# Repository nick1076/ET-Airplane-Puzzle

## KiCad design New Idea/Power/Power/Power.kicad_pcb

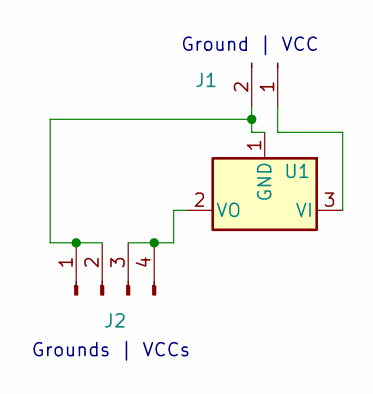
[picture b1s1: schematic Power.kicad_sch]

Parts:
J1: Conn_PinHeader_1x02_P2.54mm_Horizontal_SMD; PinHeader_UPDI_01x02_P2.54mm_Horizontal_SMD
J2: Conn_PinHeader_1x04_P2.54mm_Horizontal_SMD; PinHeader_1x04_P2.54mm_Horizontal_SMD
U1: Regulator_Linear_NCP1117-5.0V-1A; SOT-223-3_TabPin2

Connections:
unnamed: J1.1, U1.3 (VI)
unnamed: J1.2, J2.1, J2.2, U1.1 (GND)
unnamed: J2.3, J2.4, U1.2 (VO)

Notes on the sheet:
Grounds | VCCs
Ground | VCC

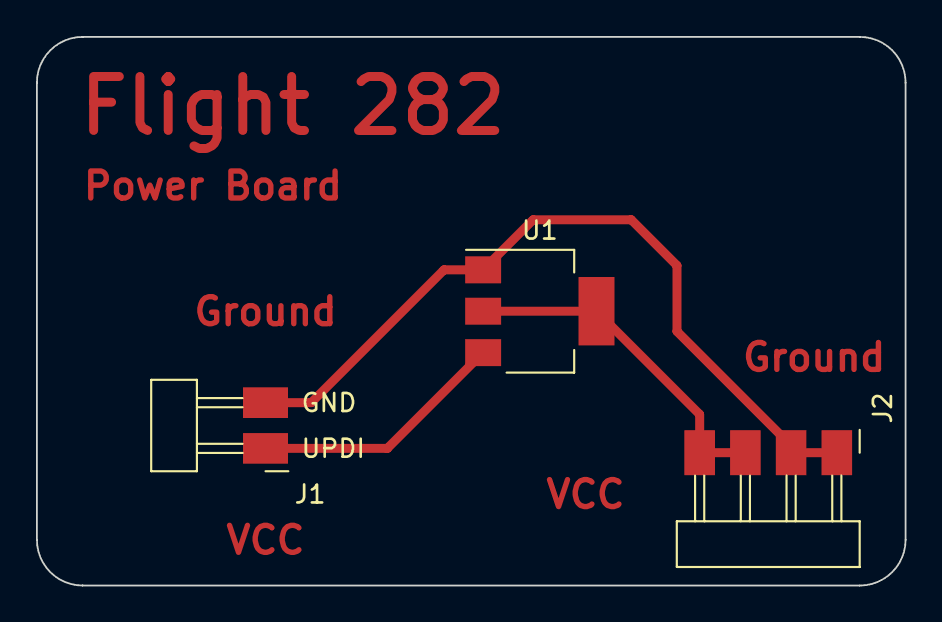
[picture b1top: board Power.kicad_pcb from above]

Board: 2 copper layers, 48.3 x 30.5 mm, 3 parts (0 on the bottom side), 3 nets.

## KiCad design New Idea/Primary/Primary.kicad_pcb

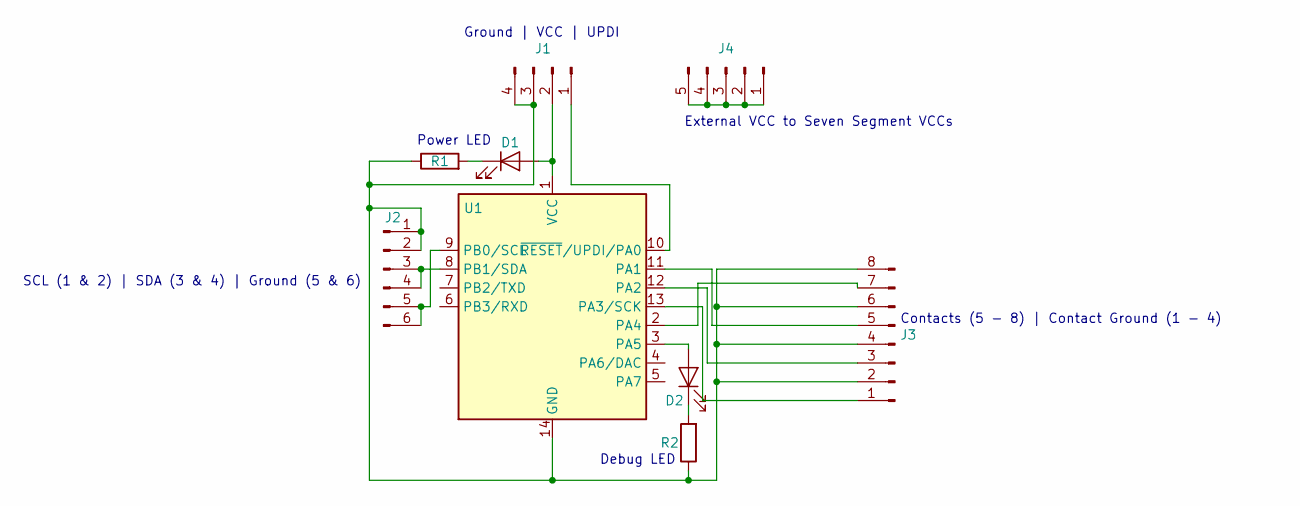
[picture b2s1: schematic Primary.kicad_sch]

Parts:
D1, D2: LED; LED_1206
J1: Conn_PinHeader_1x04_P2.54mm_Horizontal_SMD; PinHeader_1x04_P2.54mm_Horizontal_SMD
J2: Conn_PinHeader_1x06_P2.54mm_Horizontal_SMD; PinHeader_1x06_P2.54mm_Horizontal_SMD
J3: Conn_PinHeader_1x08_P2.54mm_Vertical_THT_D1.4mm; PinHeader_2x04_P2.54mm_Vertical_SMD
J4: Conn_PinHeader_1x05_P2.54mm_Horizontal_SMD; PinHeader_1x05_P2.54mm_Horizontal_SMD
R1, R2: R; R_1206
U1: Microcontroller_ATtiny1614-SSFR; SOIC-14_3.9x8.7mm_P1.27mm

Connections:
unnamed: D1.1 (K), R1.2
unnamed: D1.2 (A), J1.2, U1.1 (VCC)
unnamed: D2.1 (K), R2.2
unnamed: D2.2 (A), U1.3 (PA5)
unnamed: J1.3, J1.4, J2.1, J2.2, J3.2, J3.4, J3.6, J3.8, R1.1, R2.1, U1.14 (GND)
unnamed: J2.3, J2.4, U1.8 (PB1/SDA)
unnamed: J2.5, J2.6, U1.9 (PB0/SCL)
unnamed: J3.1, U1.13 (PA3/SCK)
unnamed: J3.3, U1.12 (PA2)
unnamed: J3.5, U1.11 (PA1)
unnamed: J3.7, U1.2 (PA4)
unnamed: J4.1, J4.2, J4.3, J4.4, J4.5
unnamed: J1.1, U1.10 (~RESET/UPDI/PA0)

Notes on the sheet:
Power LED
External VCC to Seven Segment VCCs
Debug LED
Ground | VCC | UPDI
SCL (1 & 2) | SDA (3 & 4) | Ground (5 & 6)
Contacts (5 - 8) | Contact Ground (1 - 4)

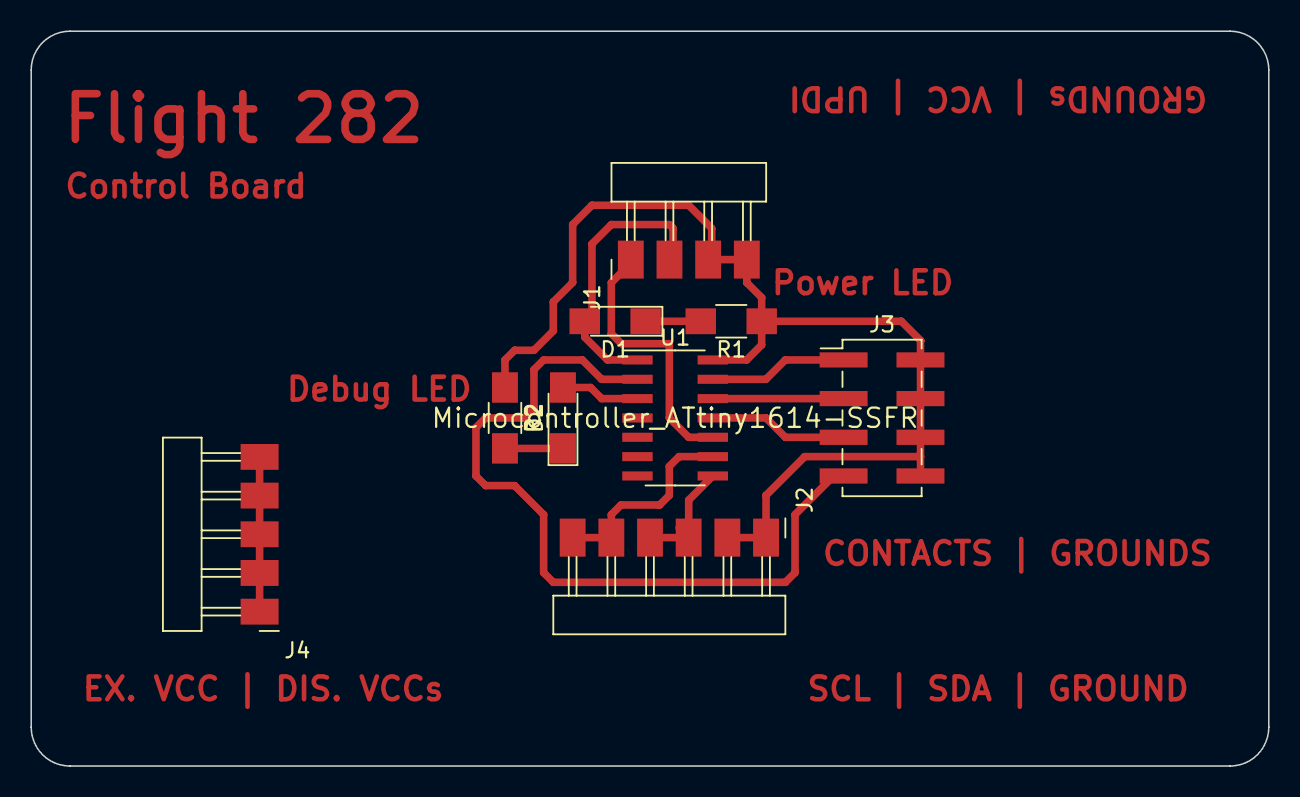
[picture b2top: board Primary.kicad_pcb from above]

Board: 2 copper layers, 81.3 x 48.3 mm, 9 parts (0 on the bottom side), 13 nets.

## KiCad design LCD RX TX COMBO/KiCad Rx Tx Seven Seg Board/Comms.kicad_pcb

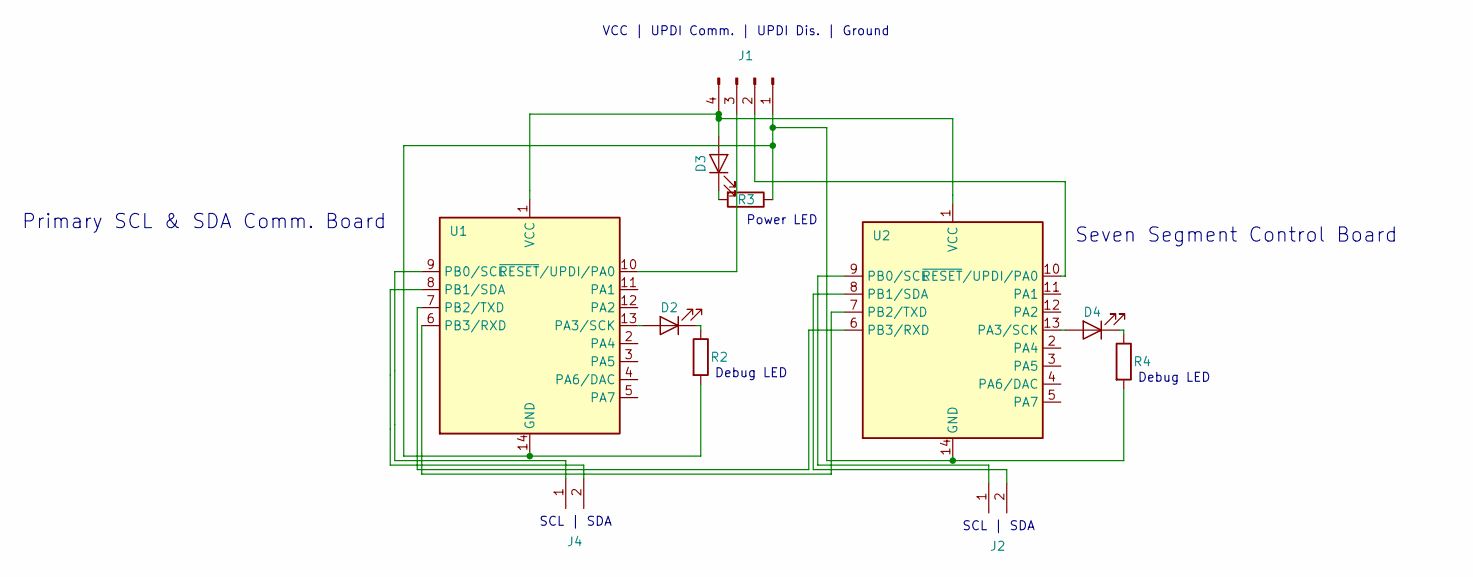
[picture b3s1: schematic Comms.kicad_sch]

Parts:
D2, D3, D4: LED; LED_1206
J1: Conn_PinHeader_1x04_P2.54mm_Horizontal_SMD; PinHeader_1x04_P2.54mm_Horizontal_SMD
J2, J4: Conn_PinHeader_1x02_P2.54mm_Horizontal_SMD; PinHeader_UPDI_01x02_P2.54mm_Horizontal_SMD
R2, R3, R4: R; R_1206
U1, U2: Microcontroller_ATtiny1614-SSFR; SOIC-14_3.9x8.7mm_P1.27mm

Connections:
unnamed: D2.1 (K), R2.1
unnamed: D2.2 (A), U1.13 (PA3/SCK)
unnamed: D3.1 (K), R3.2
unnamed: D3.2 (A), J1.4, U1.1 (VCC), U2.1 (VCC)
unnamed: D4.1 (K), R4.1
unnamed: D4.2 (A), U2.13 (PA3/SCK)
unnamed: J2.1, U2.9 (PB0/SCL)
unnamed: J2.2, U2.8 (PB1/SDA)
unnamed: J4.1, U1.9 (PB0/SCL)
unnamed: J1.1, R2.2, R3.1, R4.2, U1.14 (GND), U2.14 (GND)
unnamed: U1.6 (PB3/RXD), U2.7 (PB2/TXD)
unnamed: U1.7 (PB2/TXD), U2.6 (PB3/RXD)
unnamed: J4.2, U1.8 (PB1/SDA)
unnamed: J1.3, U1.10 (~RESET/UPDI/PA0)
unnamed: J1.2, U2.10 (~RESET/UPDI/PA0)

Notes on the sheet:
Primary SCL & SDA Comm. Board
Debug LED
Seven Segment Control Board
SCL | SDA
VCC | UPDI Comm. | UPDI Dis. | Ground
Power LED

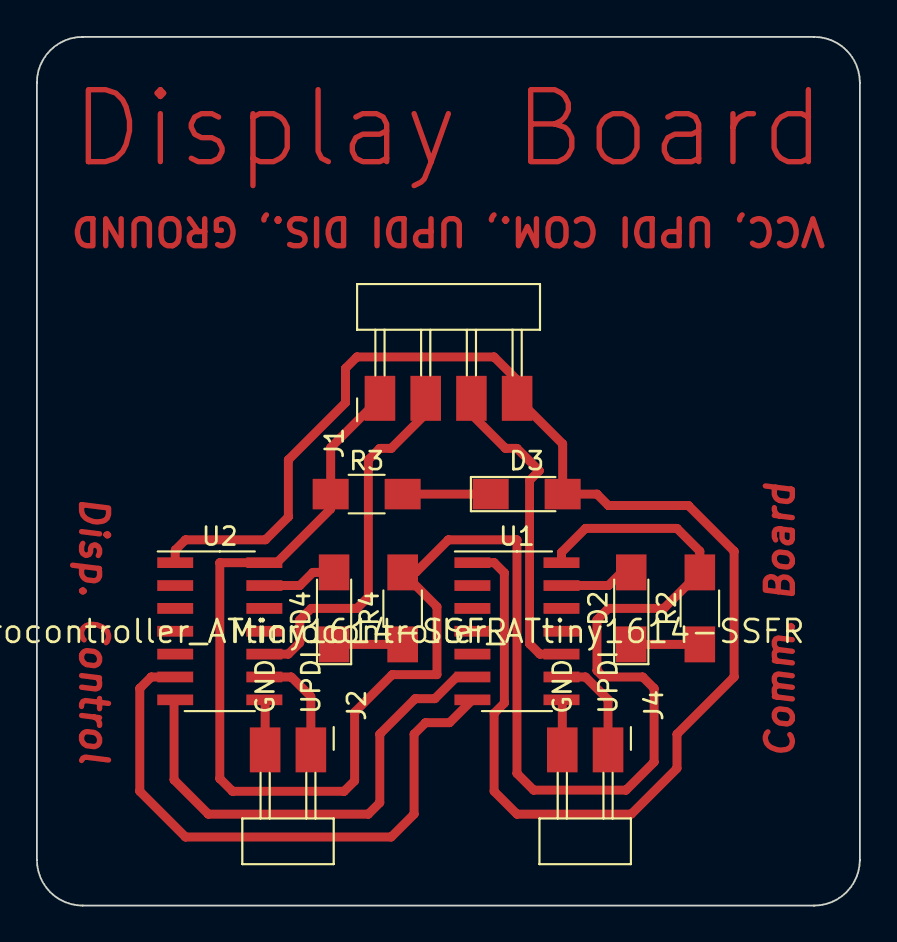
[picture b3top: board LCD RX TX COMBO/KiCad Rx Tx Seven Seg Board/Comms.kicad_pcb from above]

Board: 2 copper layers, 45.7 x 48.3 mm, 11 parts (0 on the bottom side), 15 nets.

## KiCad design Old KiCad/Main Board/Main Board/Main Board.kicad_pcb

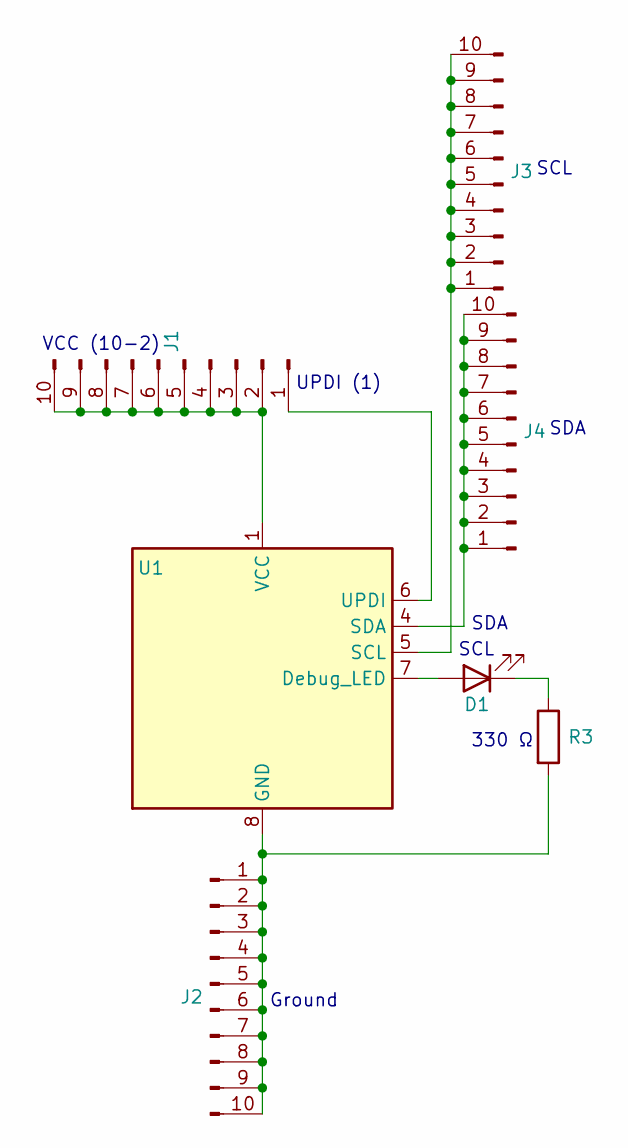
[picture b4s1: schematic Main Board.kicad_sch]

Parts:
D1: LED; LED_1206
J1, J2, J3, J4: Conn_01x10_Male; PinHeader_1x10_P2.54mm_Horizontal_SMD
R3: R; R_1206
U1: ATtiny412-SS; SOIC-8_3.9x4.9mm_P1.27mm

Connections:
unnamed: D1.1 (K), R3.1
unnamed: D1.2 (A), U1.7 (Debug_LED)
unnamed: J1.1, U1.6 (UPDI)
unnamed: J1.2, J1.3, J1.4, J1.5, J1.6, J1.7, J1.8, J1.9, J1.10, U1.1 (VCC)
unnamed: J2.1, J2.2, J2.3, J2.4, J2.5, J2.6, J2.7, J2.8, J2.9, J2.10, R3.2, U1.8 (GND)
unnamed: J3.1, J3.2, J3.3, J3.4, J3.5, J3.6, J3.7, J3.8, J3.9, J3.10, U1.5 (SCL)
unnamed: J4.1, J4.2, J4.3, J4.4, J4.5, J4.6, J4.7, J4.8, J4.9, J4.10, U1.4 (SDA)

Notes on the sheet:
SCL
VCC (10-2)
SDA
UPDI (1)
Ground
330 Ω

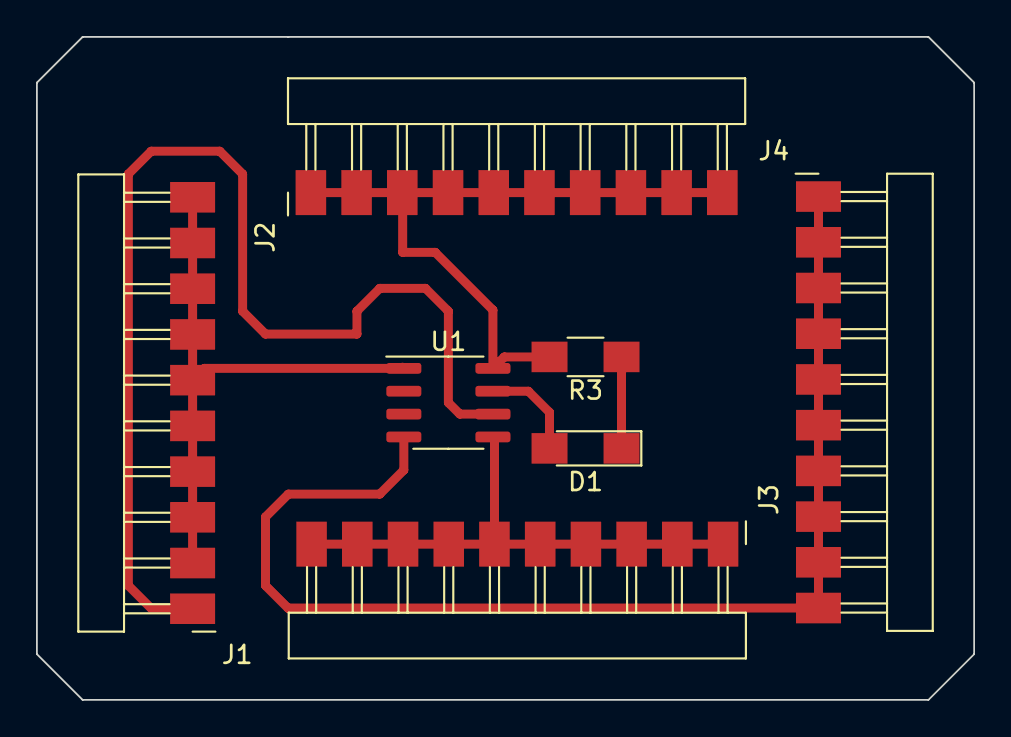
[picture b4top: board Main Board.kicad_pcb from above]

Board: 2 copper layers, 52.1 x 36.8 mm, 7 parts (0 on the bottom side), 7 nets.

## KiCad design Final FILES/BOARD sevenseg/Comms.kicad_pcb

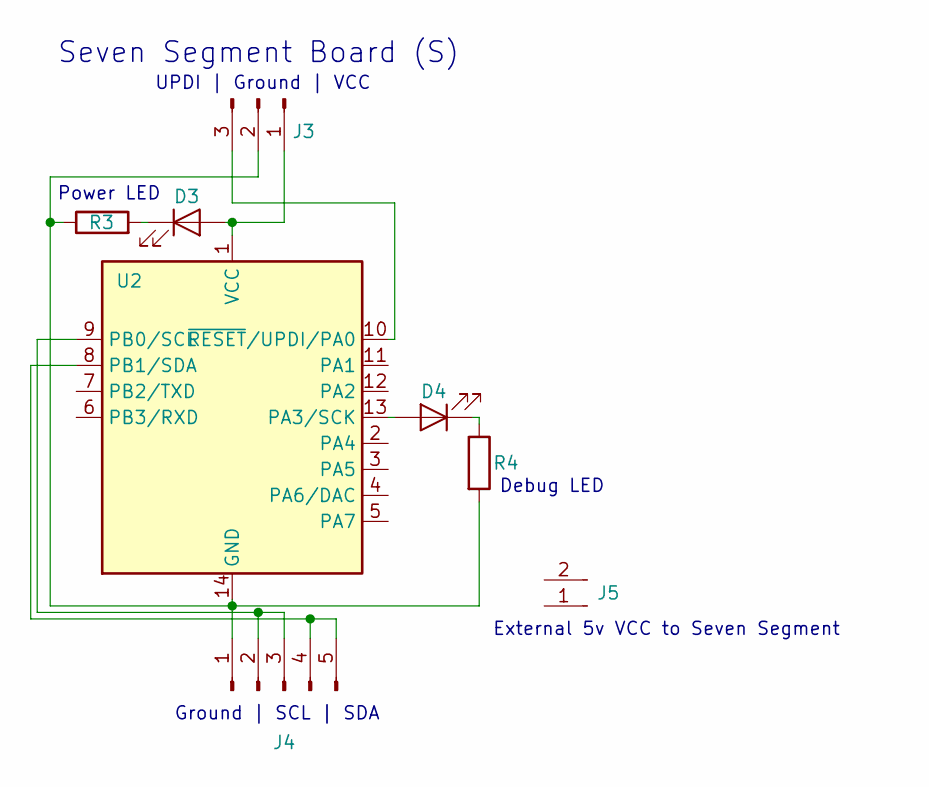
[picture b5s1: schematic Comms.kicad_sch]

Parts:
D3, D4: LED; LED_1206
J3: Conn_PinHeader_1x03_P2.54mm_Horizontal_SMD; PinHeader_1x03_P2.54mm_Horizontal_SMD
J4: Conn_PinHeader_1x05_P2.54mm_Horizontal_SMD; PinHeader_1x05_P2.54mm_Horizontal_SMD
J5: Conn_PinHeader_1x02_P2.54mm_Horizontal_SMD; PinHeader_UPDI_01x02_P2.54mm_Horizontal_SMD
R3, R4: R; R_1206
U2: Microcontroller_ATtiny1614-SSFR; SOIC-14_3.9x8.7mm_P1.27mm

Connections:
unnamed: D3.1 (K), R3.2
unnamed: D3.2 (A), J3.1, U2.1 (VCC)
unnamed: D4.1 (K), R4.1
unnamed: D4.2 (A), U2.13 (PA3/SCK)
unnamed: J3.2, J4.1, R3.1, R4.2, U2.14 (GND)
unnamed: J3.3, U2.10 (~RESET/UPDI/PA0)
unnamed: J4.2, J4.3, U2.9 (PB0/SCL)
unnamed: J4.4, J4.5, U2.8 (PB1/SDA)

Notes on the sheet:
Seven Segment Board (S)
External 5v VCC to Seven Segment
Ground | SCL | SDA
UPDI | Ground | VCC
Debug LED
Power LED

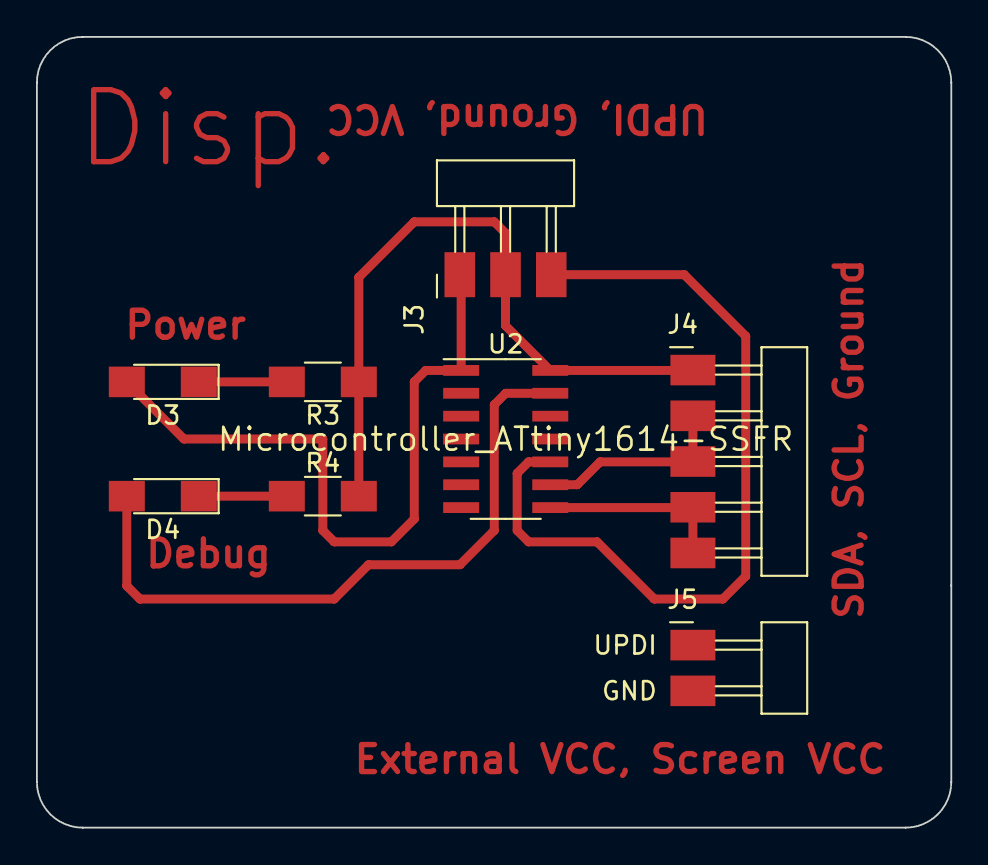
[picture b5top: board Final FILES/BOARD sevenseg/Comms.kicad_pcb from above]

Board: 2 copper layers, 50.8 x 43.9 mm, 8 parts (0 on the bottom side), 8 nets.

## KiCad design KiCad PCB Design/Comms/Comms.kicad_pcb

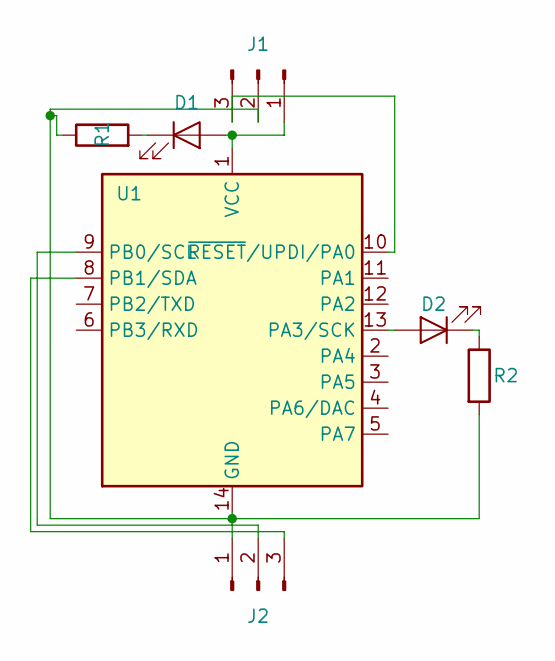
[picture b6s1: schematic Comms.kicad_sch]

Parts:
D1, D2: LED; LED_1206
J1, J2: Conn_PinHeader_1x03_P2.54mm_Horizontal_SMD; PinHeader_1x03_P2.54mm_Horizontal_SMD
R1, R2: R; R_1206
U1: Microcontroller_ATtiny1614-SSFR; SOIC-14_3.9x8.7mm_P1.27mm

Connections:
unnamed: D1.2 (A), J1.1, U1.1 (VCC)
unnamed: D2.1 (K), R2.1
unnamed: D2.2 (A), U1.13 (PA3/SCK)
unnamed: J1.2, J2.1, R1.1, R2.2, U1.14 (GND)
unnamed: J1.3, U1.10 (~RESET/UPDI/PA0)
unnamed: J2.3, U1.8 (PB1/SDA)
unnamed: D1.1 (K), R1.2
unnamed: J2.2, U1.9 (PB0/SCL)

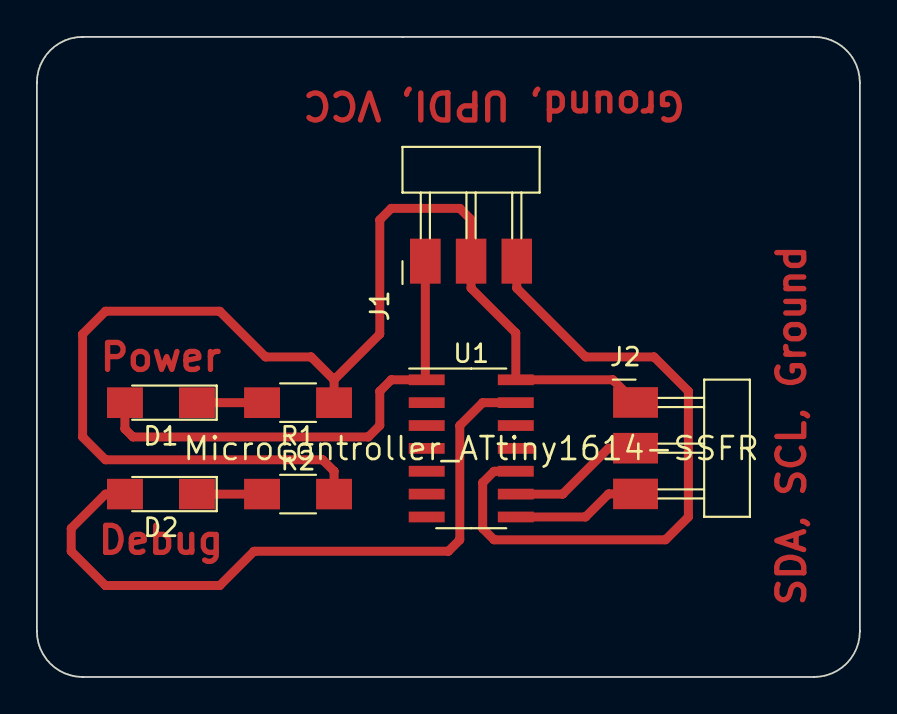
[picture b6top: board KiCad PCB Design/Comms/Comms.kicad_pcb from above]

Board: 2 copper layers, 45.7 x 35.6 mm, 7 parts (0 on the bottom side), 8 nets.

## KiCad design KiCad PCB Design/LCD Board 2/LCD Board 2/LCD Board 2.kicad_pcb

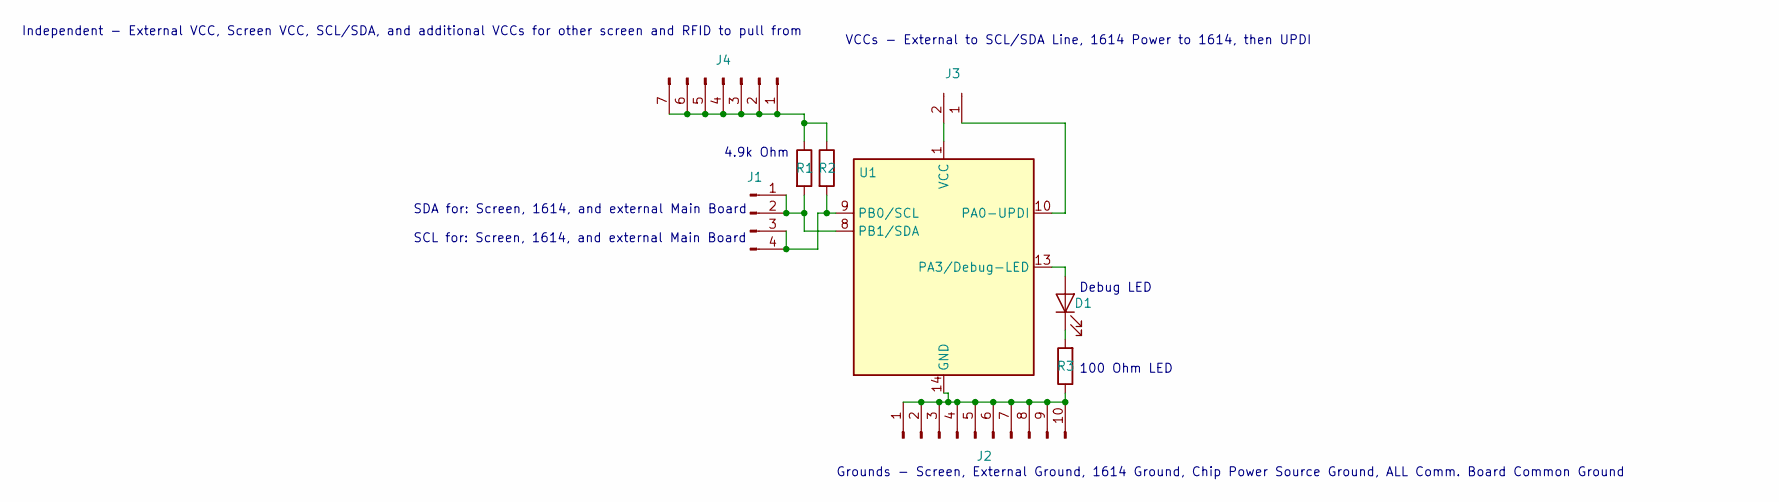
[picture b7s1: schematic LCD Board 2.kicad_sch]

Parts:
D1: LED; LED_1206
J1: Conn_PinHeader_1x04_P2.54mm_Horizontal_SMD; PinHeader_1x04_P2.54mm_Horizontal_SMD
J2: Conn_PinHeader_1x10_P2.54mm_Horizontal_SMD; PinHeader_1x10_P2.54mm_Horizontal_SMD
J3: Conn_PinHeader_1x02_P2.54mm_Horizontal_SMD; PinHeader_UPDI_01x02_P2.54mm_Horizontal_SMD
J4: Conn_PinHeader_1x07_P2.54mm_Horizontal_SMD; PinHeader_1x07_P2.54mm_Horizontal_SMD
R1, R2, R3: R; R_1206
U1: Microcontroller_ATtiny1614-SSFR; SOIC-14_3.9x8.7mm_P1.27mm

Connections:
unnamed: D1.1 (K), R3.2
unnamed: D1.2 (A), U1.13 (PA3/Debug-LED)
unnamed: J1.3, J1.4, R2.2, U1.9 (PB0/SCL)
unnamed: J3.1, U1.10 (PA0-UPDI)
unnamed: J3.2, U1.1 (VCC)
unnamed: J4.1, J4.2, J4.3, J4.4, J4.5, J4.6, J4.7, R1.1, R2.1
unnamed: J1.1, J1.2, R1.2, U1.8 (PB1/SDA)
unnamed: J2.1, J2.2, J2.3, J2.4, J2.5, J2.6, J2.7, J2.8, J2.9, J2.10, R3.1, U1.14 (GND)

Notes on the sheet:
Debug LED
Grounds - Screen, External Ground, 1614 Ground, Chip Power Source Ground, ALL Comm. Board Common Ground
Independent - External VCC, Screen VCC, SCL/SDA, and additional VCCs for other screen and RFID to pull from
100 Ohm LED
VCCs - External to SCL/SDA Line, 1614 Power to 1614, then UPDI
SDA for: Screen, 1614, and external Main Board SCL for: Screen, 1614, and external Main Board
4.9k Ohm

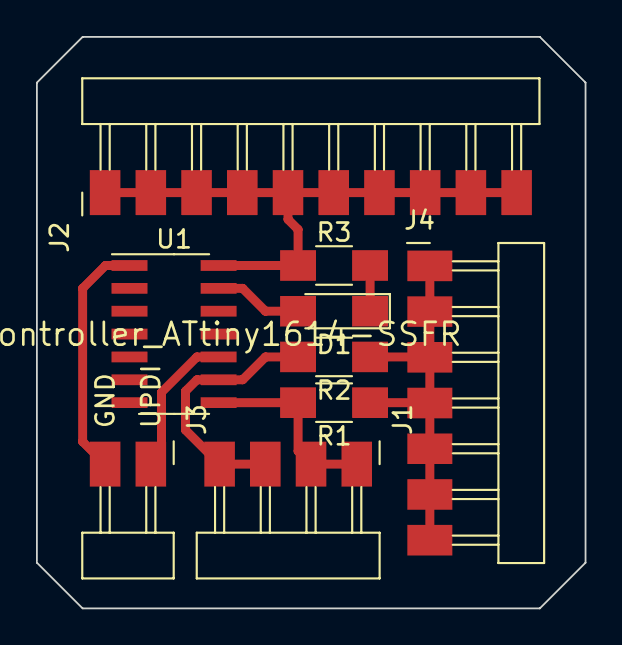
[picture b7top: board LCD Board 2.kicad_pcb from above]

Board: 2 copper layers, 30.5 x 31.8 mm, 9 parts (0 on the bottom side), 8 nets.

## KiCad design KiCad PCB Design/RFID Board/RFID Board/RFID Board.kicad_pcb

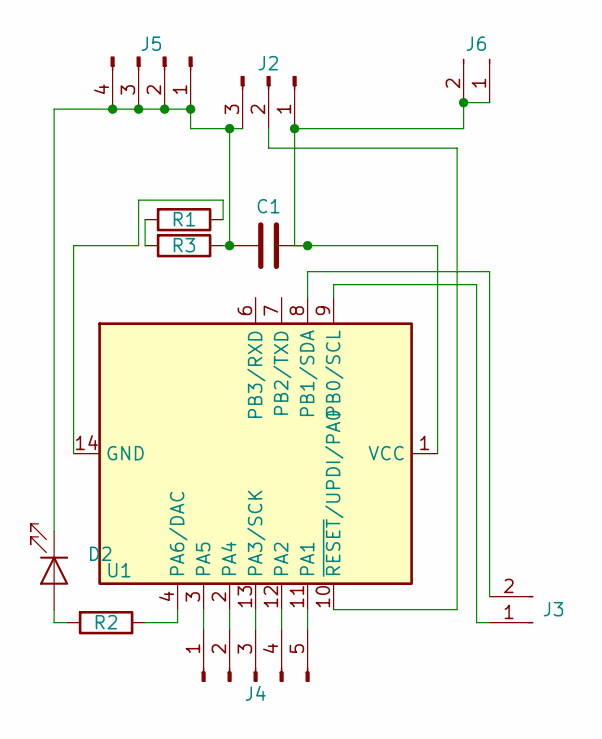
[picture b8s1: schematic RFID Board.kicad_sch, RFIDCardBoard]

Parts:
C1: C; C_1206
D2: LED; LED_1206
J2: Microcontroller_Ground_UPDI_Power; PinHeader_1x03_P2.54mm_Horizontal_SMD
J3: SDA SCL; PinHeader_UPDI_01x02_P2.54mm_Horizontal_SMD
J4: RFID_CC; PinHeader_1x05_P2.54mm_Horizontal_SMD
J5: Ground_Rail; PinHeader_1x04_P2.54mm_Horizontal_SMD
J6: Power_Rail; PinHeader_UPDI_01x02_P2.54mm_Horizontal_SMD
R1, R2, R3: R; R_1206
U1: Microcontroller_ATtiny1614-SSFR; SOIC-14_3.9x8.7mm_P1.27mm

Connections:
unnamed: C1.2, J2.1, J6.1, J6.2, U1.1 (VCC)
unnamed: C1.1, D2.1 (K), J2.3, J5.1, J5.2, J5.3, J5.4, R3.1
unnamed: D2.2 (A), R2.2
unnamed: J2.2, U1.10 (~RESET/UPDI/PA0)
unnamed: J3.1, U1.9 (PB0/SCL)
unnamed: J3.2, U1.8 (PB1/SDA)
unnamed: J4.1, U1.3 (PA5)
unnamed: J4.2, U1.2 (PA4)
unnamed: J4.3, U1.13 (PA3/SCK)
unnamed: J4.4, U1.12 (PA2)
unnamed: J4.5, U1.11 (PA1)
unnamed: R1.2, R3.2
unnamed: R2.1, U1.4 (PA6/DAC)
unnamed: R1.1, U1.14 (GND)

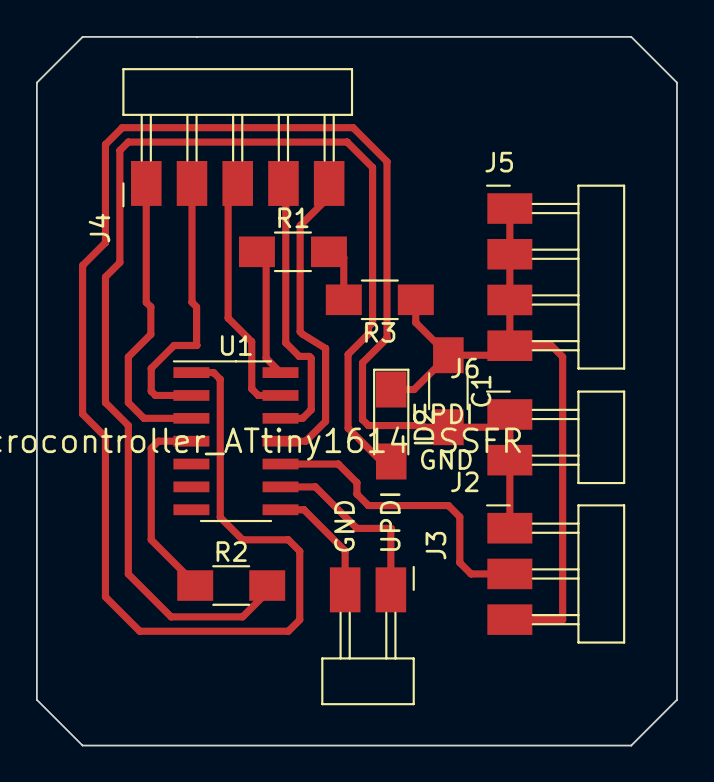
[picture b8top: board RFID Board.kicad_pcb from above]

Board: 2 copper layers, 35.6 x 39.4 mm, 11 parts (0 on the bottom side), 14 nets.

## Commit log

2022-10-16 v1.0 - Initial
    Initial code push.
2022-10-30 v1.1 - Working Arduino Proto Code
2022-11-06 v1.2 - KiCad Work
2022-11-08 v1.3 - Main PCB Board Updated To Fab Library
2022-11-19 v1.4 - Unknown Updates
    Not sure what was changed but I want to push updates.
2022-11-22 v1.5 - Code Refactoring & Organization
2022-11-29 v1.6 - KiCad & Code Additions
2022-11-30 v1.7 - Further KiCad Dev
2022-11-30 v1.8 - LCD Dev
2022-12-01 v1.9 - KiCad LCD Board Updates
2022-12-02 v2.0 - i2C Testing Boards Designed
2022-12-03 v2.1 - Working i2c for arduino + kiCad design
2022-12-05 v2.2 - WORKING I2C
2022-12-05 v2.3 - Important Delay Update
2022-12-05 v2.4 - Final i2C code updates
2022-12-06 v2.5 - LCD Board Design & Code
2022-12-07 v2.6 - LCD 2.0
2022-12-07 v2.7 - Display Codes & Design
2022-12-07 v2.8 - NEW IDEA
2022-12-07 v2.9 - KiCad Finished
2022-12-07 v3.0 - New Board Code
2022-12-08 v3.1 - Board Updates
2022-12-08 v3.2 - Final
2022-12-11 v3.3 - Power Supply Board Design
2022-12-12 v3.4 - KiCad and Code Updates
2022-12-12 v3.5 - Code Updates, Mill File, 3D Models
